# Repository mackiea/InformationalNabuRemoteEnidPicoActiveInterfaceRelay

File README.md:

# InformationalNabuRemoteEnidPicoActiveInterfaceRelay
Allows interfacing from the NABU PC to the Raspberry Pi Pico via [ENID] (github.com/mackiea/ExternalNabuInterfaceDevice).

## Features
- 5 unused GPIO signals exposed
- Can be powered from the ENID 5V supply or from USB

## Pinout

| ENID | Pico GPIO Pin | Description           |
| ---- | ------------- | -----------           |
|    1 |            27 | Interrupt Request     |
|    2 |            26 | Interrupt Acknowledge |
|    3 |      Not used | 3.58 MHz Clock        |
|    4 |      Not used | Audio                 |
|    5 |            22 | Card Select           |
|    6 |             2 | Address 0             |
|    7 |             3 | Address 1             |
|    8 |             4 | Address 2             |
|    9 |             5 | Address 3             |
|   10 |      Not used | 1.79 MHz Clock        |
|   11 |            21 | Write                 |
|   12 |            20 | Read                  |
|   13 |            19 | I/O Request           |
|   14 |            28 | Wait Request          |
|   15 |      Not Used | Reset                 |
|   16 |             6 | Data 0                |
|   17 |             7 | Data 1                |
|   18 |             8 | Data 2                |
|   19 |             9 | Data 3                |
|   20 |            10 | Data 4                |
|   21 |            11 | Data 5                |
|   22 |            12 | Data 6                |
|   23 |            13 | Data 7                |
|   24 |          VSYS | +5V Rail 1 (Switched) |
|   25 |    PCB Ground | Ground Rail 1         |

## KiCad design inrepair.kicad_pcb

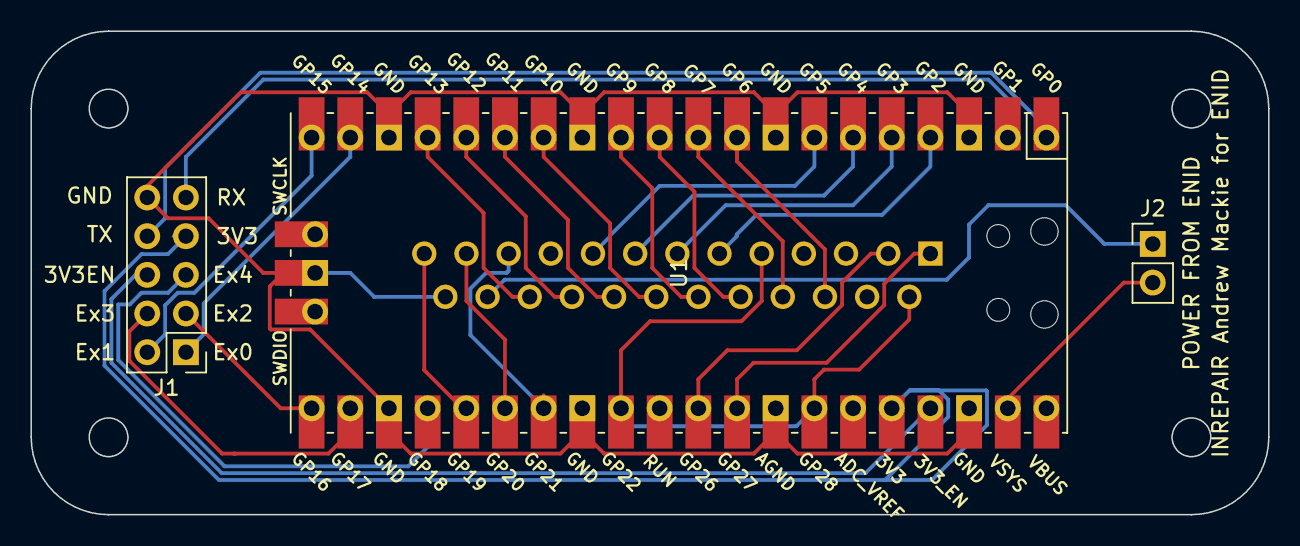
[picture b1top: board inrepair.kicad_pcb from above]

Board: 2 copper layers, 81.3 x 31.8 mm, 4 parts (1 on the bottom side), 31 nets.

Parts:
ENID1: DB25_Male_MountingHoles; DSUB-25_Male_Vertical_P2.77x2.84mm
J1: EXTRAS; PinHeader_2x05_P2.54mm_Vertical
J2: POWER_FROM_ENID; PinHeader_1x02_P2.54mm_Vertical
U1: Pico; RPi_Pico_SMD_TH

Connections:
3V3: J1.7, U1.36
3V3_EN: J1.6, U1.37
+5V_1: ENID1.24, J2.1
ADDRESS_0: ENID1.6, U1.4
ADDRESS_1: ENID1.7, U1.5
ADDRESS_2: ENID1.8, U1.6
ADDRESS_3: ENID1.9, U1.7
CARD_SELECT: ENID1.5, U1.29
DATA_0: ENID1.16, U1.9
DATA_1: ENID1.17, U1.10
DATA_2: ENID1.18, U1.11
DATA_3: ENID1.19, U1.12
DATA_4: ENID1.20, U1.14
DATA_5: ENID1.21, U1.15
DATA_6: ENID1.22, U1.16
DATA_7: ENID1.23, U1.17
EXTRA_0: J1.1, U1.19
EXTRA_1: J1.2, U1.20
EXTRA_2: J1.3, U1.21
EXTRA_3: J1.4, U1.22
EXTRA_4: J1.5, U1.24
GND: ENID1.25, J1.10, U1.3, U1.8, U1.13, U1.18, U1.23, U1.28, U1.33, U1.38, U1.42
INTERRUPT_ACKNOWLEDGE: ENID1.2, U1.31
INTERRUPT_REQUEST: ENID1.1, U1.32
IO_REQUEST: ENID1.13, U1.25
READ: ENID1.12, U1.26
RX: J1.9, U1.2
TX: J1.8, U1.1
VSYS: J2.2, U1.39
WAIT_REQUEST: ENID1.14, U1.34
WRITE: ENID1.11, U1.27

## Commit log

2023-04-09 Added KiCAD files.
2023-04-12 Added license.
2023-04-12 Added URL to PCB; added images.
2023-04-12 ENID wconnector connections were reversed. Oopsie poopsie.
